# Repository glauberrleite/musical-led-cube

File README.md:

# Musical LED Cube
A RGB LED Cube that follows the music through its audio spectrum.

## Requirements

* scipy
* numpy
* matplotlib
* pyaudio

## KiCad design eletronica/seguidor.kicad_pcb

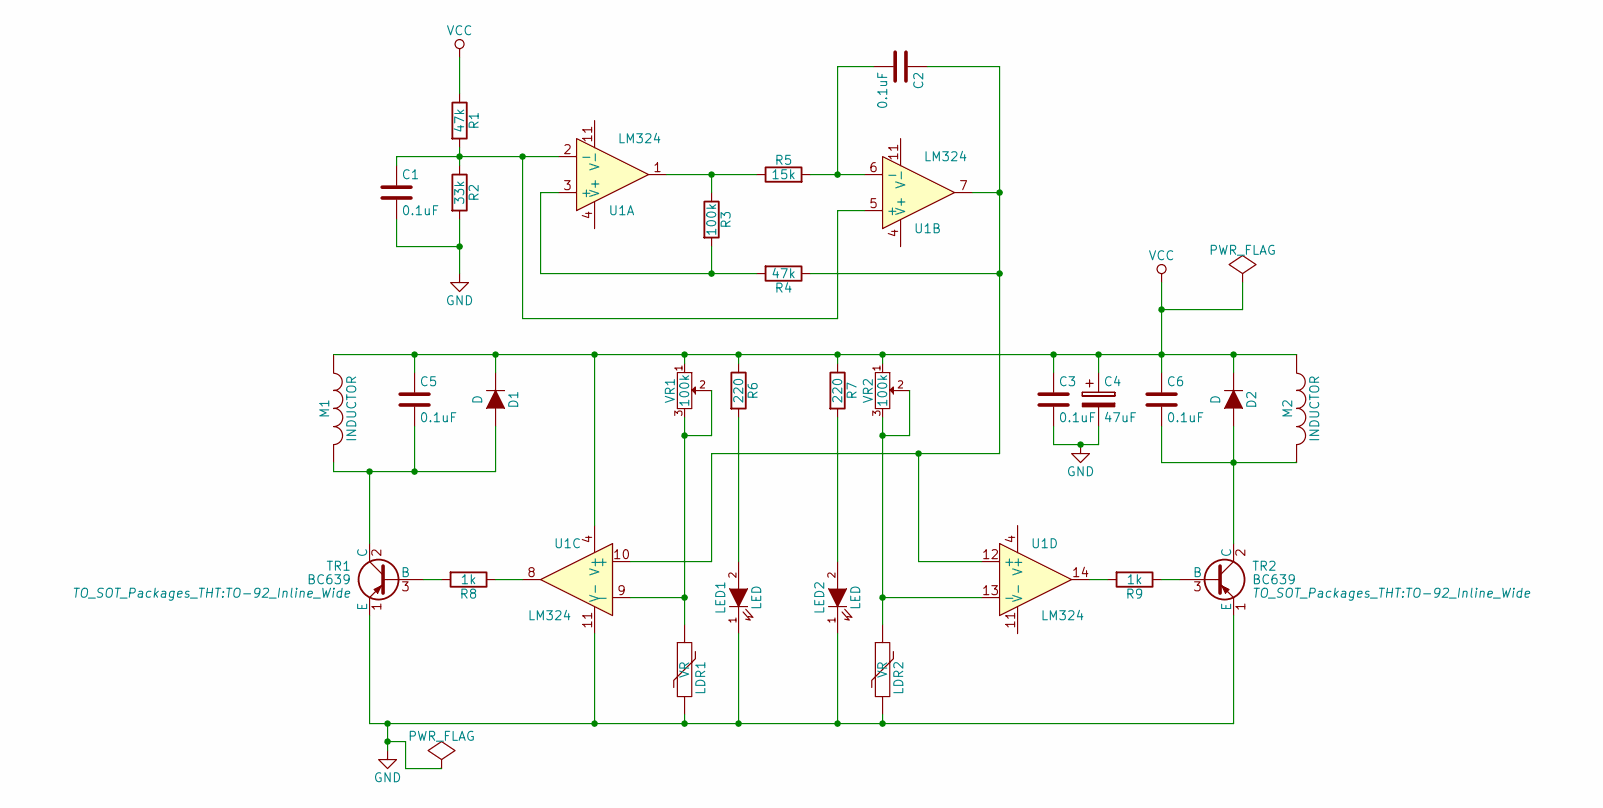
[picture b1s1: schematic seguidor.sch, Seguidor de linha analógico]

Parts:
C1, C2, C3, C5, C6: 0.1uF; C_Disc_D6_P5
C4: 47uF; C_Radial_D5_L11_P2
D1, D2: D; Diode_DO-35_SOD27_Horizontal_RM10
LDR1, LDR2: VR; Pin_Header_Straight_2x01
LED1, LED2: LED; Pin_Header_Straight_2x01
M1, M2: INDUCTOR; Pin_Header_Straight_2x01
R1, R4: 47k; Resistor_Horizontal_RM10mm
R2: 33k; Resistor_Horizontal_RM10mm
R3: 100k; Resistor_Horizontal_RM10mm
R5: 15k; Resistor_Horizontal_RM10mm
R6, R7: 220; Resistor_Horizontal_RM10mm
R8, R9: 1k; Resistor_Horizontal_RM10mm
TR1, TR2: BC639; TO-92_Inline_Wide
U1: LM324; DIP-14_W7.62mm
VR1, VR2: 100k; Potentiometer_Bourns_3296P_3-8Zoll_Angular_ScrewFront

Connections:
GND: C1.2, C3.2, C4.2, LDR1.2, LDR2.2, LED1.1 (K), LED2.1 (K), R2.2, TR1.1 (E), TR2.1 (E), U1.11 (V-); also elsewhere on the board
unnamed: C1.1, R1.2, R2.1, U1.2 (-), U1.5 (+)
unnamed: C2.1, R4.1, U1.7, U1.10 (+), U1.12 (+)
unnamed: C2.2, R5.2, U1.6 (-)
unnamed: C5.2, D1.2 (A), M1.2, TR1.2 (C)
unnamed: C6.2, D2.2 (A), M2.2, TR2.2 (C)
unnamed: LDR1.1, U1.9 (-), VR1.2, VR1.3
unnamed: LDR2.1, U1.13 (-), VR2.2, VR2.3
unnamed: LED1.2 (A), R6.2
unnamed: LED2.2 (A), R7.2
unnamed: R3.1, R5.1, U1.1
unnamed: R3.2, R4.2, U1.3 (+)
unnamed: R8.1, U1.8
unnamed: R8.2, TR1.3 (B)
unnamed: R9.1, TR2.3 (B)
unnamed: R9.2, U1.14
VCC: C3.1, C4.1, C5.1, C6.1, D1.1 (K), D2.1 (K), M1.1, M2.1, R1.1, R6.1, R7.1, U1.4 (V+), VR1.1, VR2.1; also elsewhere on the board

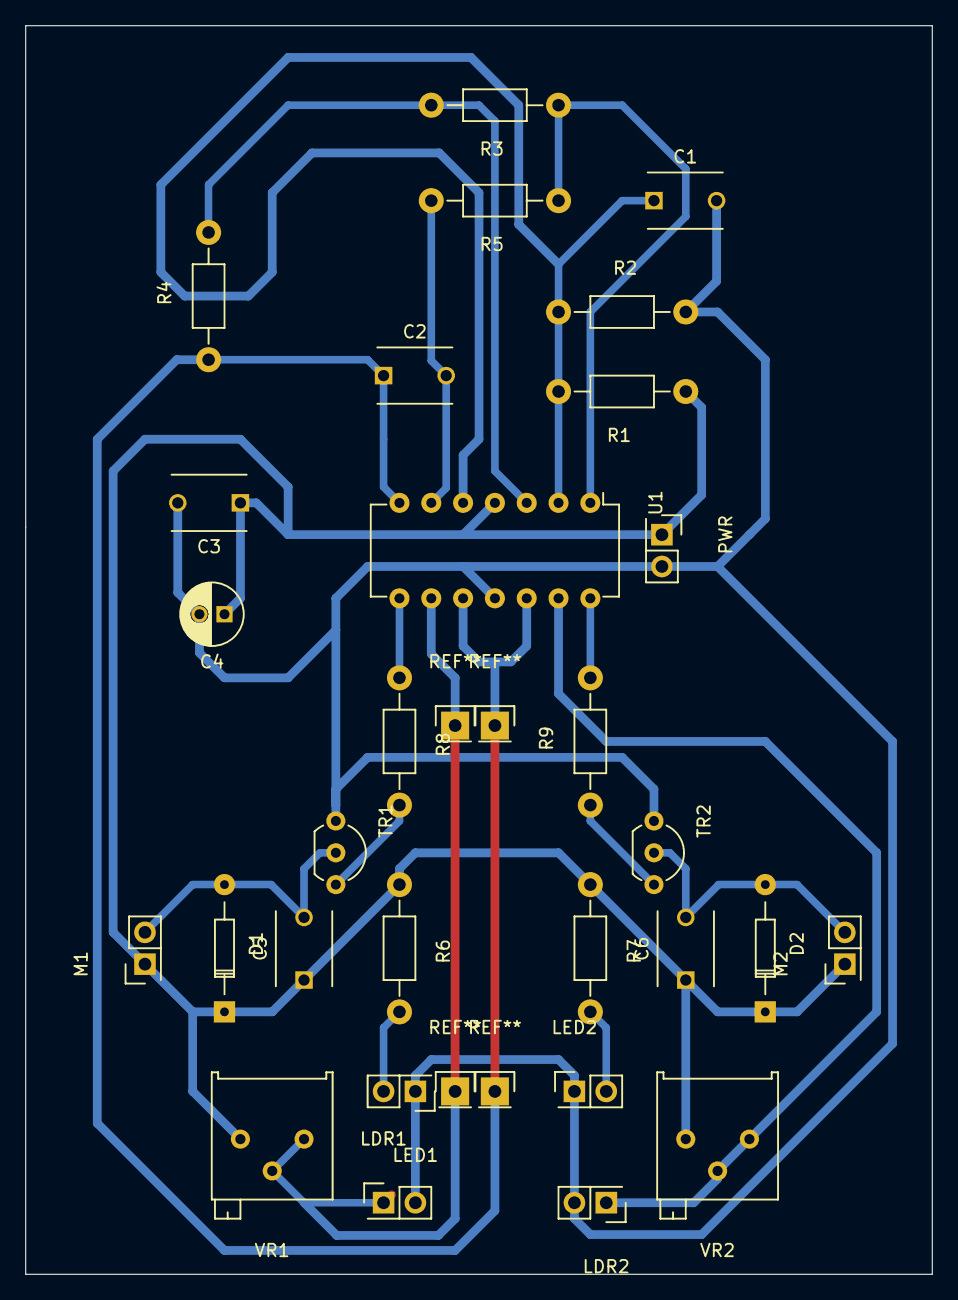
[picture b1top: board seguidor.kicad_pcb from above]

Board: 2 copper layers, 72.4 x 99.7 mm, 29 parts (0 on the bottom side), 17 nets.

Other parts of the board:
PWR: Battery; Pin_Header_Straight_2x01

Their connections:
GND: PWR.2; also elsewhere on the board
VCC: PWR.1; also elsewhere on the board

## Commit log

2017-10-23 Uploading audio sample
2017-10-23 main file
2017-10-23 Testing spectrum
2017-10-23 Fix on plotSpectrum
2017-10-23 Using matplotlib
2017-10-23 Added dependencies
2017-10-26 Converted sample wav from stereo to mono
2017-10-26 spectrum class
2017-10-27 Errors corrections
2017-10-27 Adjusted a little the intro of the song
2017-10-27 playSample plays the music for testing purposes
2017-10-27 Animation working and bash script added
2017-10-27 New requirement on README
2017-10-27 Comments
2017-10-27 added fft
2017-10-27 Code from a nice guy, done right
2017-11-07 Dudu's berry
2017-11-13 arduino 2.0
2017-12-06 Projeto do carrinho
2017-12-08 Almost
2017-12-08 ALMOSSSST!
2017-12-08 done
2017-12-08 Added print file
